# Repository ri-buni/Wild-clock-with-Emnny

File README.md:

# Wild-clock-with-Emnny
Emnny is a small AI powered mascot. When I say the wake word, he wakes up, listens to me and answers in his own voice. The rest of the time, he just shows current time and quietly exists!

# PCB
Made in KiCad

Schematic

PCB

# Case
Made in Fusion360

# Firmware
Was written by Claude Code

# BOM

- [INMP441](https://aliexpress.ru/item/1005004862555297.html?spm=a2g2w.cart.cart_split.21.77b34aa6A5IoAS&sku_id=12000030790772841)
- [Speakers](https://aliexpress.ru/item/1005007315336158.html?spm=a2g2w.cart.cart_split.19.77b34aa6A5IoAS&sku_id=12000040230074388)
- [Amplifier chip](https://aliexpress.ru/item/1005006942750928.html?spm=a2g2w.cart.cart_split.17.77b34aa6A5IoAS&sku_id=12000057389651708)
- [ESP32 S3 WROOM 1](https://aliexpress.ru/item/1005005567013022.html?spm=a2g2w.cart.cart_split.15.77b34aa6A5IoAS&sku_id=12000033579387192)
- [Buttons](https://aliexpress.ru/item/1005007623070623.html?spm=a2g2w.cart.cart_split.13.77b34aa6A5IoAS&sku_id=12000041542638533)
- [LiPo 3.7V 2000mah](https://aliexpress.ru/item/1005008217717191.html?spm=a2g2w.cart.cart_split.11.77b34aa6A5IoAS&sku_id=12000044268208531)
- [TP4056 chip](https://aliexpress.ru/item/32714366180.html?spm=a2g2w.cart.cart_split.9.77b34aa6A5IoAS&sku_id=61056856324)
- [LDO](https://aliexpress.ru/item/1005004159688937.html?spm=a2g2w.cart.cart_split.8.77b34aa6A5IoAS&sku_id=12000028232628606)
- [Display](https://aliexpress.ru/item/1005008770450001.html?spm=a2g2w.cart.cart_split.6.77b34aa6A5IoAS&sku_id=12000046598711076)
- [USBLC6 2SC6](https://aliexpress.ru/item/1005009468432448.html?spm=a2g2w.cart.cart_split.4.77b34aa6A5IoAS&sku_id=12000049196393604)
- [USB Type C connector](https://aliexpress.ru/item/1005007694777041.html?spm=a2g2w.cart.cart_split.2.77b34aa6A5IoAS&sku_id=12000041875830363)
Total ~35$

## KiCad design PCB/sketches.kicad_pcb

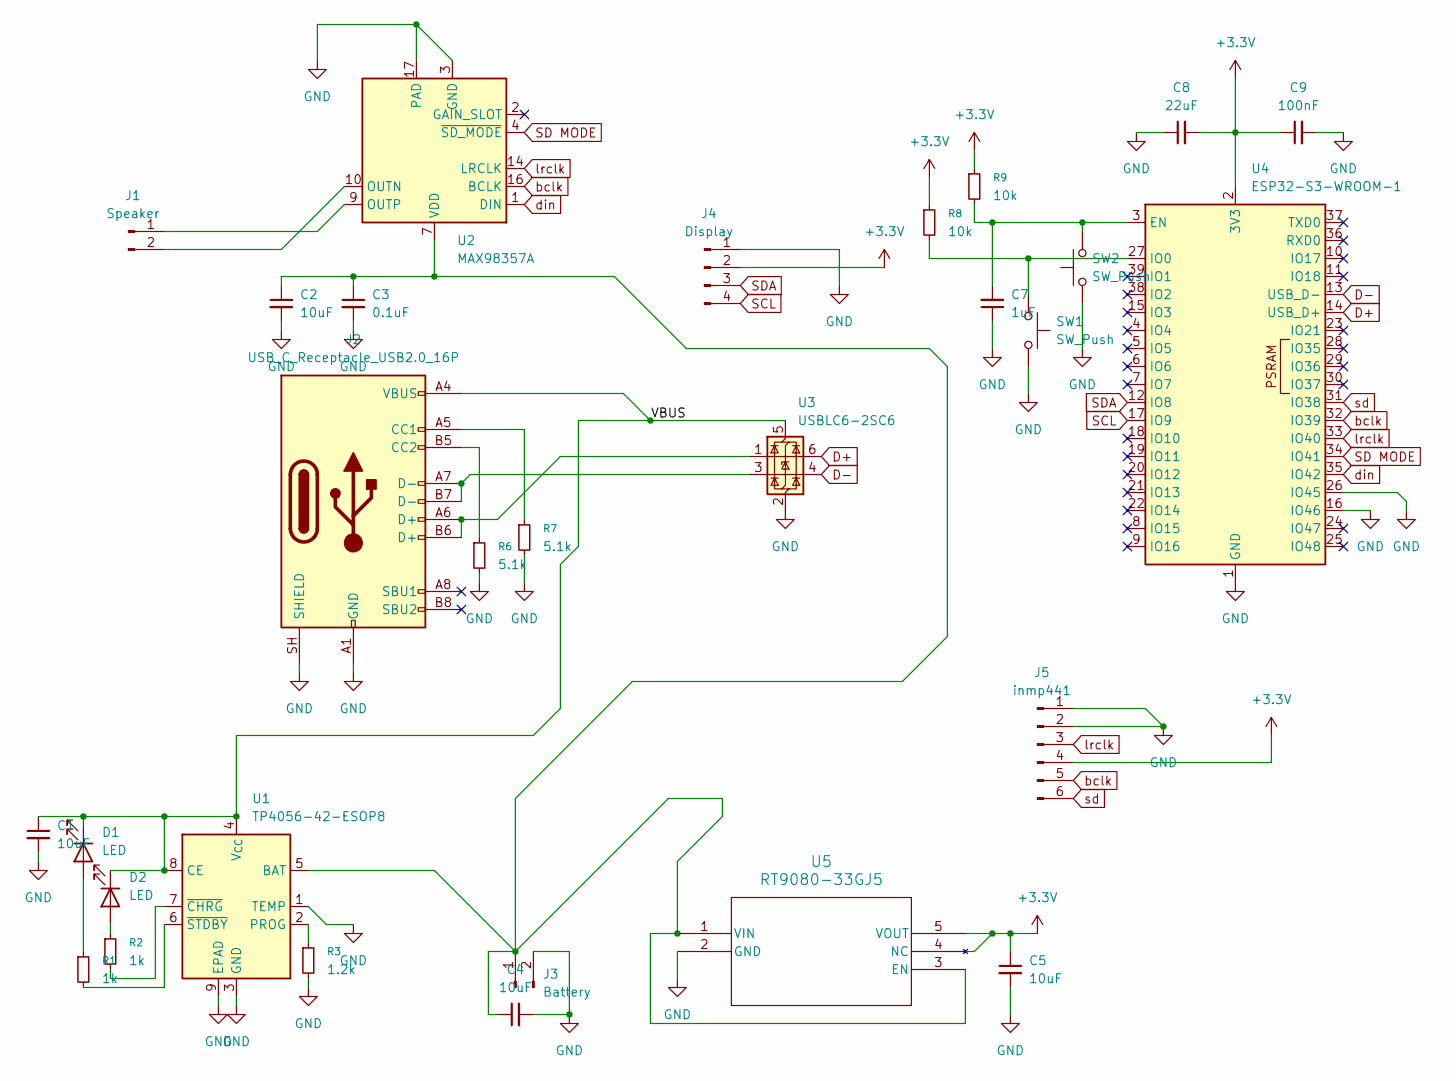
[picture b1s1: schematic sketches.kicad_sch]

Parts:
C1, C2, C4, C5: 10uF; C_0603_1608Metric
C3: 0.1uF; C_0603_1608Metric
C7: 1uF; C_0603_1608Metric
C8: 22uF; C_0603_1608Metric
C9: 100nF; C_0603_1608Metric
D1, D2: LED; LED_D3.0mm
J1: Speaker; PinHeader_1x02_P2.54mm_Vertical
J2: USB_C_Receptacle_USB2.0_16P; USB_C_Receptacle_HRO_TYPE-C-31-M-12
J3: Battery; PinHeader_1x02_P2.54mm_Vertical
J4: Display; PinHeader_1x04_P2.54mm_Vertical
J5: inmp441; PinHeader_1x06_P2.54mm_Vertical
R1, R2: 1k; R_0603_1608Metric
R3: 1.2k; R_0603_1608Metric
R6, R7: 5.1k; R_0603_1608Metric
R8, R9: 10k; R_0603_1608Metric
SW1, SW2: SW_Push; SW_SPST_PTS645Sx43SMTR92
U1: TP4056-42-ESOP8; SOIC-8-1EP_3.9x4.9mm_P1.27mm_EP2.41x3.3mm_ThermalVias
U2: MAX98357A; TQFN-16-1EP_3x3mm_P0.5mm_EP1.23x1.23mm
U3: USBLC6-2SC6; SOT-23-6
U4: ESP32-S3-WROOM-1
U5: RT9080-33GJ5; TSOT-23-5_RIT

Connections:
+3.3V: C5.1, C8.2, C9.1, J4.2, J5.4, R8.1, R9.1, U4.2 (3V3), U5.4 (NC), U5.5 (VOUT)
/VBUS: C1.1, D1.1 (K), D2.1 (K), J2.A4 (VBUS), J2.A9 (VBUS), J2.B4 (VBUS), J2.B9 (VBUS), U1.4 (V_{CC}), U1.8 (CE), U3.5 (VBUS)
D+: U3.6 (I/O1), U4.14 (USB_D+)
D-: U3.4 (I/O2), U4.13 (USB_D-)
GND: C1.2, C2.2, C3.2, C4.2, C5.2, C7.1, C8.1, C9.2, J2.A1 (GND), J2.A12 (GND), J2.B1 (GND), J2.B12 (GND), J2.SH (SHIELD), J3.2, J4.1, J5.1, J5.2, R3.2, R6.2, R7.2, SW1.2, SW2.1, U1.1 (TEMP), U1.3 (GND), U1.9 (EPAD), U2.3 (GND), U2.11 (GND), U2.15 (GND), U2.17 (PAD), U3.2 (GND), U4.1 (GND), U4.16 (IO46), U4.26 (IO45), U4.40 (GND), U4.41 (GND), U5.2 (GND)
unnamed: D1.2 (A), R1.1
unnamed: D2.2 (A), R2.1
unnamed: J1.1, U2.9 (OUTP)
unnamed: J1.2, U2.10 (OUTN)
unnamed: J2.A5 (CC1), R7.1
unnamed: J2.B5 (CC2), R6.1
unnamed: J2.A6 (D+), J2.B6 (D+), U3.1 (I/O1)
unnamed: J2.A7 (D-), J2.B7 (D-), U3.3 (I/O2)
unnamed: C2.1, C3.1, C4.1, J3.1, U1.5 (BAT), U2.7 (VDD), U2.8 (VDD), U5.1 (VIN), U5.3 (EN)
unnamed: R3.1, U1.2 (PROG)
unnamed: R2.2, U1.7 (~CHRG)
unnamed: R1.2, U1.6 (~STDBY)
unnamed: C7.2, R9.2, SW2.2, U4.3 (EN)
unnamed: R8.2, SW1.1, U4.27 (IO0)
SCL: J4.4, U4.17 (IO9)
SD MODE: U2.4 (~SD_MODE), U4.34 (IO41)
SDA: J4.3, U4.12 (IO8)
bclk: J5.5, U2.16 (BCLK), U4.32 (IO39)
din: U2.1 (DIN), U4.35 (IO42)
lrclk: J5.3, U2.14 (LRCLK), U4.33 (IO40)
sd: J5.6, U4.31 (IO38)

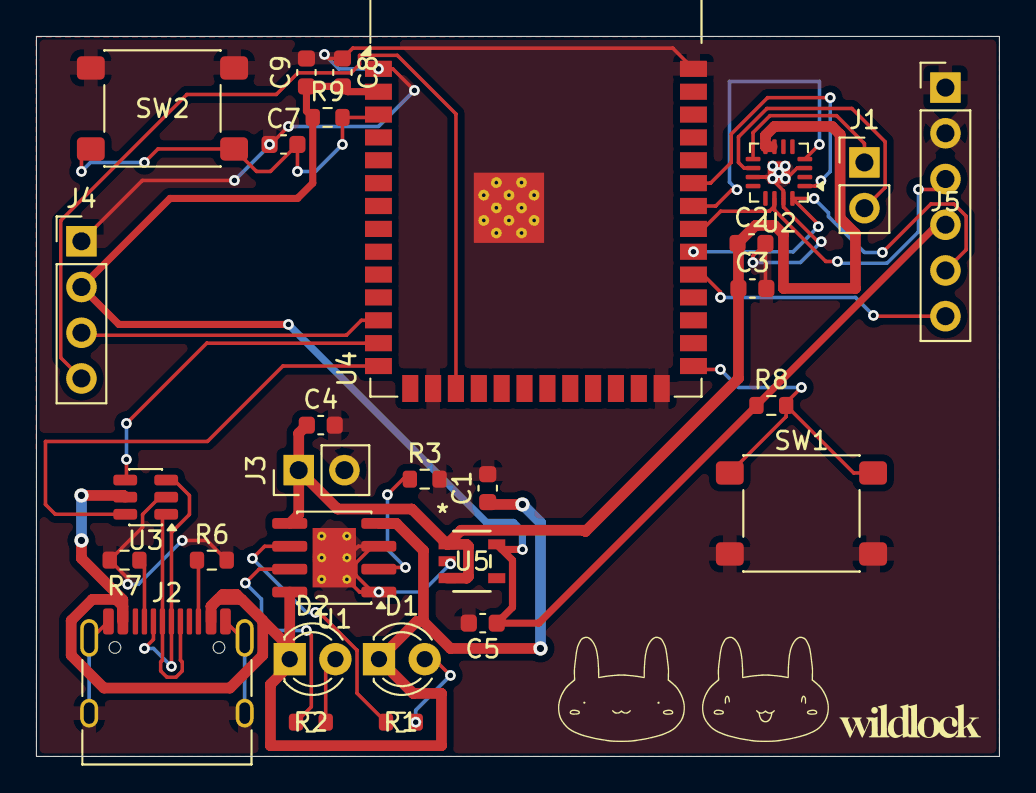
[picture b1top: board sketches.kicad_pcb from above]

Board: 2 copper layers, 53.5 x 40.0 mm, 29 parts (0 on the bottom side), 26 nets.

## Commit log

2026-05-20 Create a
2026-05-20 Create as
2026-05-20 Create s
2026-05-20 Create didnt make it yet
